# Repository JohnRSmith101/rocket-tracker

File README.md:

# Rocket Tracker

A system that tracks and video-records rockets as they climb into space. A
motorized telescope-and-camera gimbal is steered by an operator until a small
tracking camera sees the rocket. A neural-network detector on a Raspberry Pi 5
then takes over and keeps the rocket centered while the telescope camera
records.

The complete story of why it is built this way, and how to build one yourself,
is in the **Build Book** (see below). This repository has the software,
trained models, hardware design files and training dataset.

## How it works

1. An operator slews the system by joystick, looking through a finder scope, to
   bring the rising rocket into the tracking camera's field of view.
2. A Raspberry Pi 5 runs an object detector (YOLO11n, exported to NCNN) on the
   tracking camera's video. Each time it detects the rocket, it plays an alert
   sound. This tells the operator, who cannot look at a screen, to release the
   joystick trigger.
3. The Pi sends the rocket's position and velocity to an Arduino Due over USB
   serial. The Arduino runs closed-loop PID control of the azimuth and
   elevation stepper motors to keep the rocket centered. The telescope's own
   camera (a Canon EOS 70D on a Celestron C5) records the launch.
4. When detections stop, the alert stops, and the operator can take over.

## What is where

| Folder | Contents |
|---|---|
| `software/gimbal-controller/` | Arduino Due sketches: gimbal controller, and a version that logs PID data |
| `software/tracker-yolo/` | Raspberry Pi 5 tracking program using the YOLO11n model (current) |
| `software/tracker-tflite-legacy/` | Earlier tracking program using a TensorFlow Lite model (kept for reference) |
| `models/yolo/` | The trained YOLO model that Rocket Tracker uses, and training results |
| `models/tflite-ssd-oct2024/` | The earlier TensorFlow Lite model, used by the legacy tracker |
| `models/mediapipe-dec2024/` | A MediaPipe Model Maker model from December 2024, with training records |
| `datasets/` | The 633-image training dataset (documentation here, files in a Release) |
| `hardware/kicad/` | KiCad files and Gerbers for the Gimbal Controller Box and Lid circuit boards |
| `hardware/3d-printing/` | STL files for the 3D-printed parts (print in PETG) |
| `docs/` | Original drawings (the Build Book itself is on the Releases page) |
| `LICENSES/`, `LICENSE`, `NOTICE` | Licensing and credits |

## Downloads (large files)

GitHub limits file sizes in the repository, so these are on the
[Releases page](../../releases):

- **Build Book** (PDF and Word): the full design document
- `rocket-tracker-dataset-633-images.zip`: all images, with YOLO, Pascal VOC and COCO-JSON annotations
- `data.zip`: the same dataset packaged for the YOLO training notebook in Google Colab
- `yolo-training-runs-full.zip`: all three YOLO training runs with weights and plots

## Quick start (YOLO tracker)

1. Build the hardware following the Build Book.
2. On the Raspberry Pi 5, follow the Build Book section "Deploying YOLO models to Raspberry Pi 5", or see `software/tracker-yolo/README.md`.
3. Upload `software/gimbal-controller/Rocket_Tracker_2026_R14` to the Arduino Due.

## Status and limits

- The YOLO model was trained on only 633 images, many of them near-duplicates, and some classes
  have very few examples. Expect it to work best in conditions similar to the training footage.
  See `datasets/README.md`.
- The author built and tested this one system. Other hardware may need changes.
- The TensorFlow Lite and MediaPipe material is kept as a record; the YOLO tracker supersedes it.

## Safety

Motorized mounts can pinch fingers, and optics can cause permanent eye damage if pointed at the
sun. Build and operate at your own risk. See `LICENSE`.

## License

Open source, with different licenses for different parts: Apache-2.0 (Arduino and TFLite
software), AGPL-3.0 (YOLO tracker and models), CC BY-SA 4.0 (Build Book, hardware, datasets).
Details in `LICENSE`. Credits to the projects this builds on are in `NOTICE`.

Copyright 2026 John R. Smith.

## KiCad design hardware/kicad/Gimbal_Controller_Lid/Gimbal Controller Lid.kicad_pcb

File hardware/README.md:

# Hardware

License: CC BY-SA 4.0.

- `kicad/`: KiCad projects for the Gimbal Controller circuit boards (**Box** and **Lid**). Each folder has the KiCad project, schematic and PCB files, a picture, and a zip of the Gerber and drill files for ordering boards.
- `3d-printing/`: one folder per part, each with an STL file and a preview picture. Print in PETG. The parts were designed in the Morphi app (iPad) and sliced in Ultimaker Cura for an Ender 3 printer. See the Build Book, Appendix A, for the parts list and photos.

The Build Book has the wiring, the complete parts list, and assembly instructions.

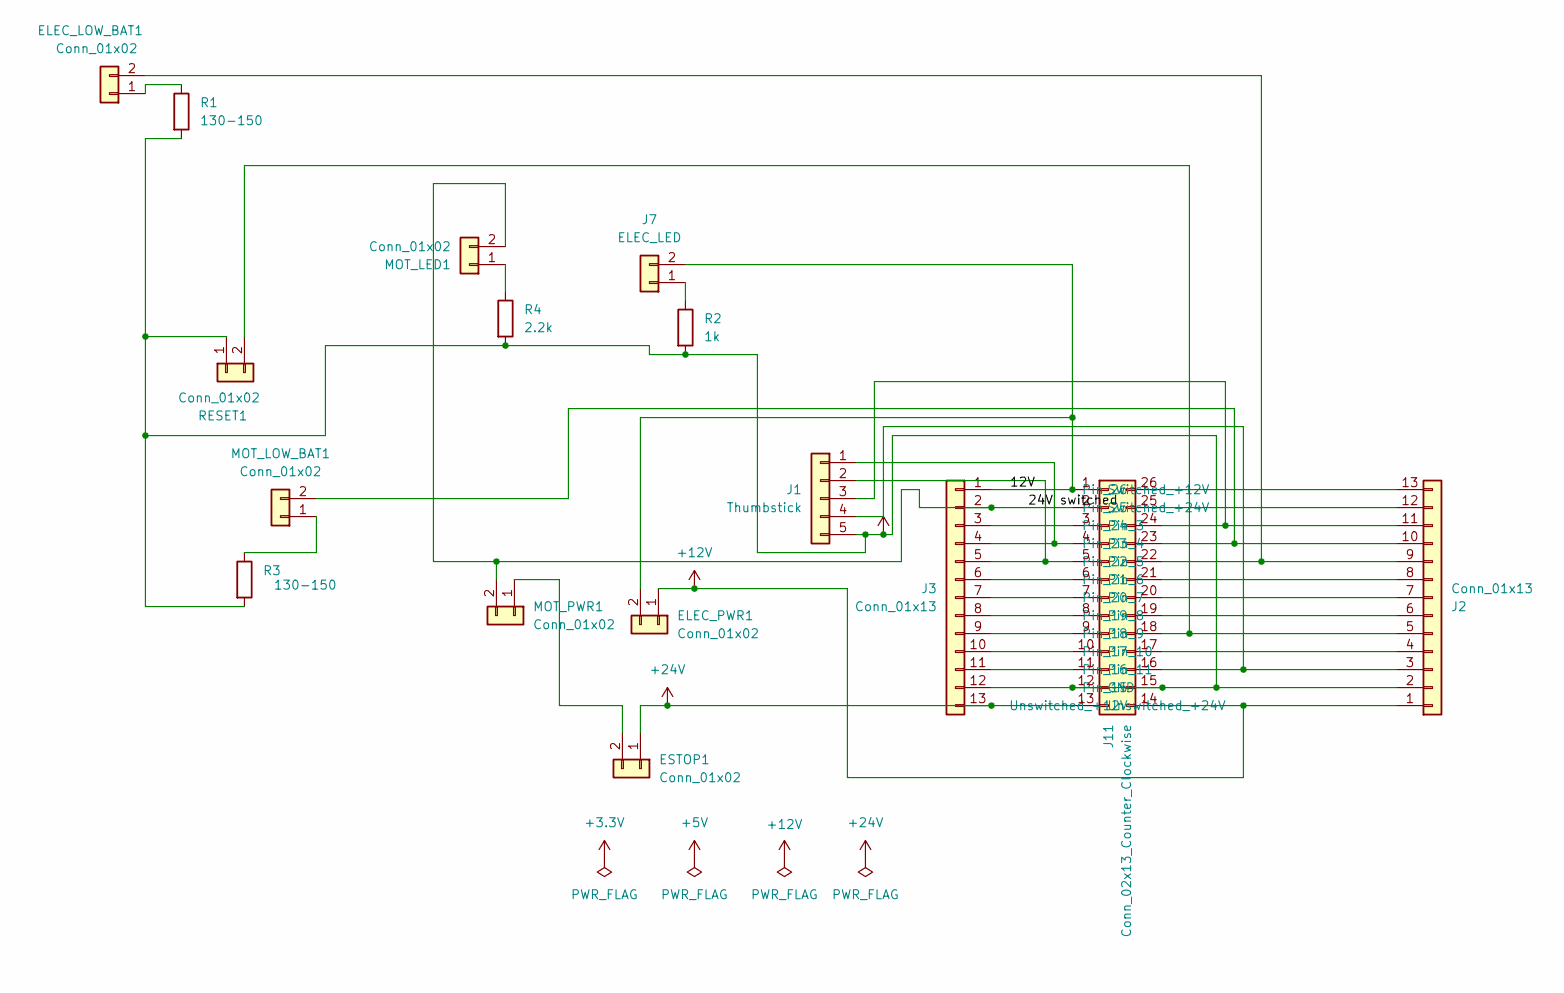
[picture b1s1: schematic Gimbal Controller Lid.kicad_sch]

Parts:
ELEC_LOW_BAT1: Conn_01x02; PinSocket_1x02_P2.54mm_Vertical
ELEC_PWR1: Conn_01x02; PinSocket_1x02_P2.54mm_Vertical
ESTOP1: Conn_01x02; PinSocket_1x02_P2.54mm_Vertical
J1: Thumbstick; PinHeader_1x05_P2.54mm_Vertical
J2, J3: Conn_01x13; PinSocket_1x13_P2.54mm_Vertical
J7: ELEC_LED; PinSocket_1x02_P2.54mm_Vertical
J11: Conn_02x13_Counter_Clockwise; IDC-Header_2x13_P2.54mm_Vertical
MOT_LED1: Conn_01x02; PinSocket_1x02_P2.54mm_Vertical
MOT_LOW_BAT1: Conn_01x02; PinSocket_1x02_P2.54mm_Vertical
MOT_PWR1: Conn_01x02; PinSocket_1x02_P2.54mm_Vertical
R1, R3: 130-150; R_Axial_DIN0204_L3.6mm_D1.6mm_P7.62mm_Horizontal
R2: 1k; R_Axial_DIN0204_L3.6mm_D1.6mm_P7.62mm_Horizontal
R4: 2.2k; R_Axial_DIN0204_L3.6mm_D1.6mm_P7.62mm_Horizontal
RESET1: Conn_01x02; PinSocket_1x02_P2.54mm_Vertical

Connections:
+5V: J1.5, J2.2, J3.12, J11.12 (GND), J11.15, R1.2, R2.2, R3.2, R4.2, RESET1.1
+12V: ELEC_PWR1.1, J2.1, J11.14 (Unswitched_+12V)
+24V: ESTOP1.1, J3.13, J11.13 (Unswitched_+24V)
/12V: ELEC_PWR1.2, J3.1, J7.2, J11.1 (Switched_+12V)
/24V switched: J3.2, J11.2 (Switched_+24V), MOT_LED1.2, MOT_PWR1.2
unnamed: ELEC_LOW_BAT1.1, R1.1
unnamed: ELEC_LOW_BAT1.2, J2.9, J11.22
unnamed: ESTOP1.2, MOT_PWR1.1
unnamed: J1.1, J3.4, J11.4
unnamed: J1.2, J3.5, J11.5
unnamed: J1.3, J2.11, J11.24
unnamed: J1.4, J2.3, J11.16
unnamed: J7.1, R2.1
unnamed: J3.3, J11.3
unnamed: J3.6, J11.6
unnamed: J3.7, J11.7
unnamed: J3.8, J11.8
unnamed: J3.9, J11.9
unnamed: J3.10, J11.10
unnamed: J3.11, J11.11
unnamed: J2.4, J11.17
unnamed: J2.5, J11.18, RESET1.2
unnamed: J2.6, J11.19
unnamed: J2.7, J11.20
unnamed: J2.8, J11.21
unnamed: J2.10, J11.23, MOT_LOW_BAT1.2
unnamed: J2.12, J11.25
unnamed: J2.13, J11.26
unnamed: MOT_LED1.1, R4.1
unnamed: MOT_LOW_BAT1.1, R3.1

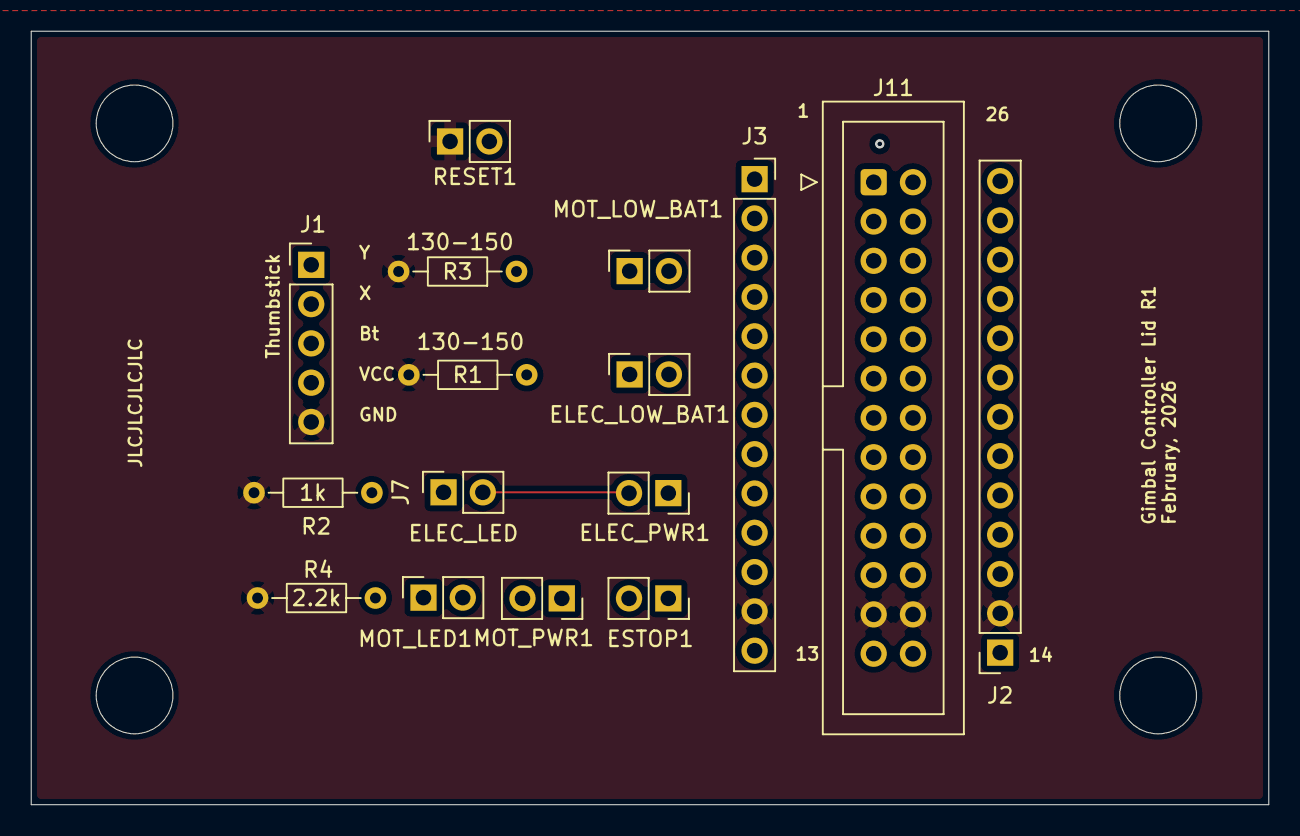
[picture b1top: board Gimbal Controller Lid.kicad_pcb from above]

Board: 4 copper layers, 80.0 x 50.0 mm, 16 parts (0 on the bottom side), 30 nets.

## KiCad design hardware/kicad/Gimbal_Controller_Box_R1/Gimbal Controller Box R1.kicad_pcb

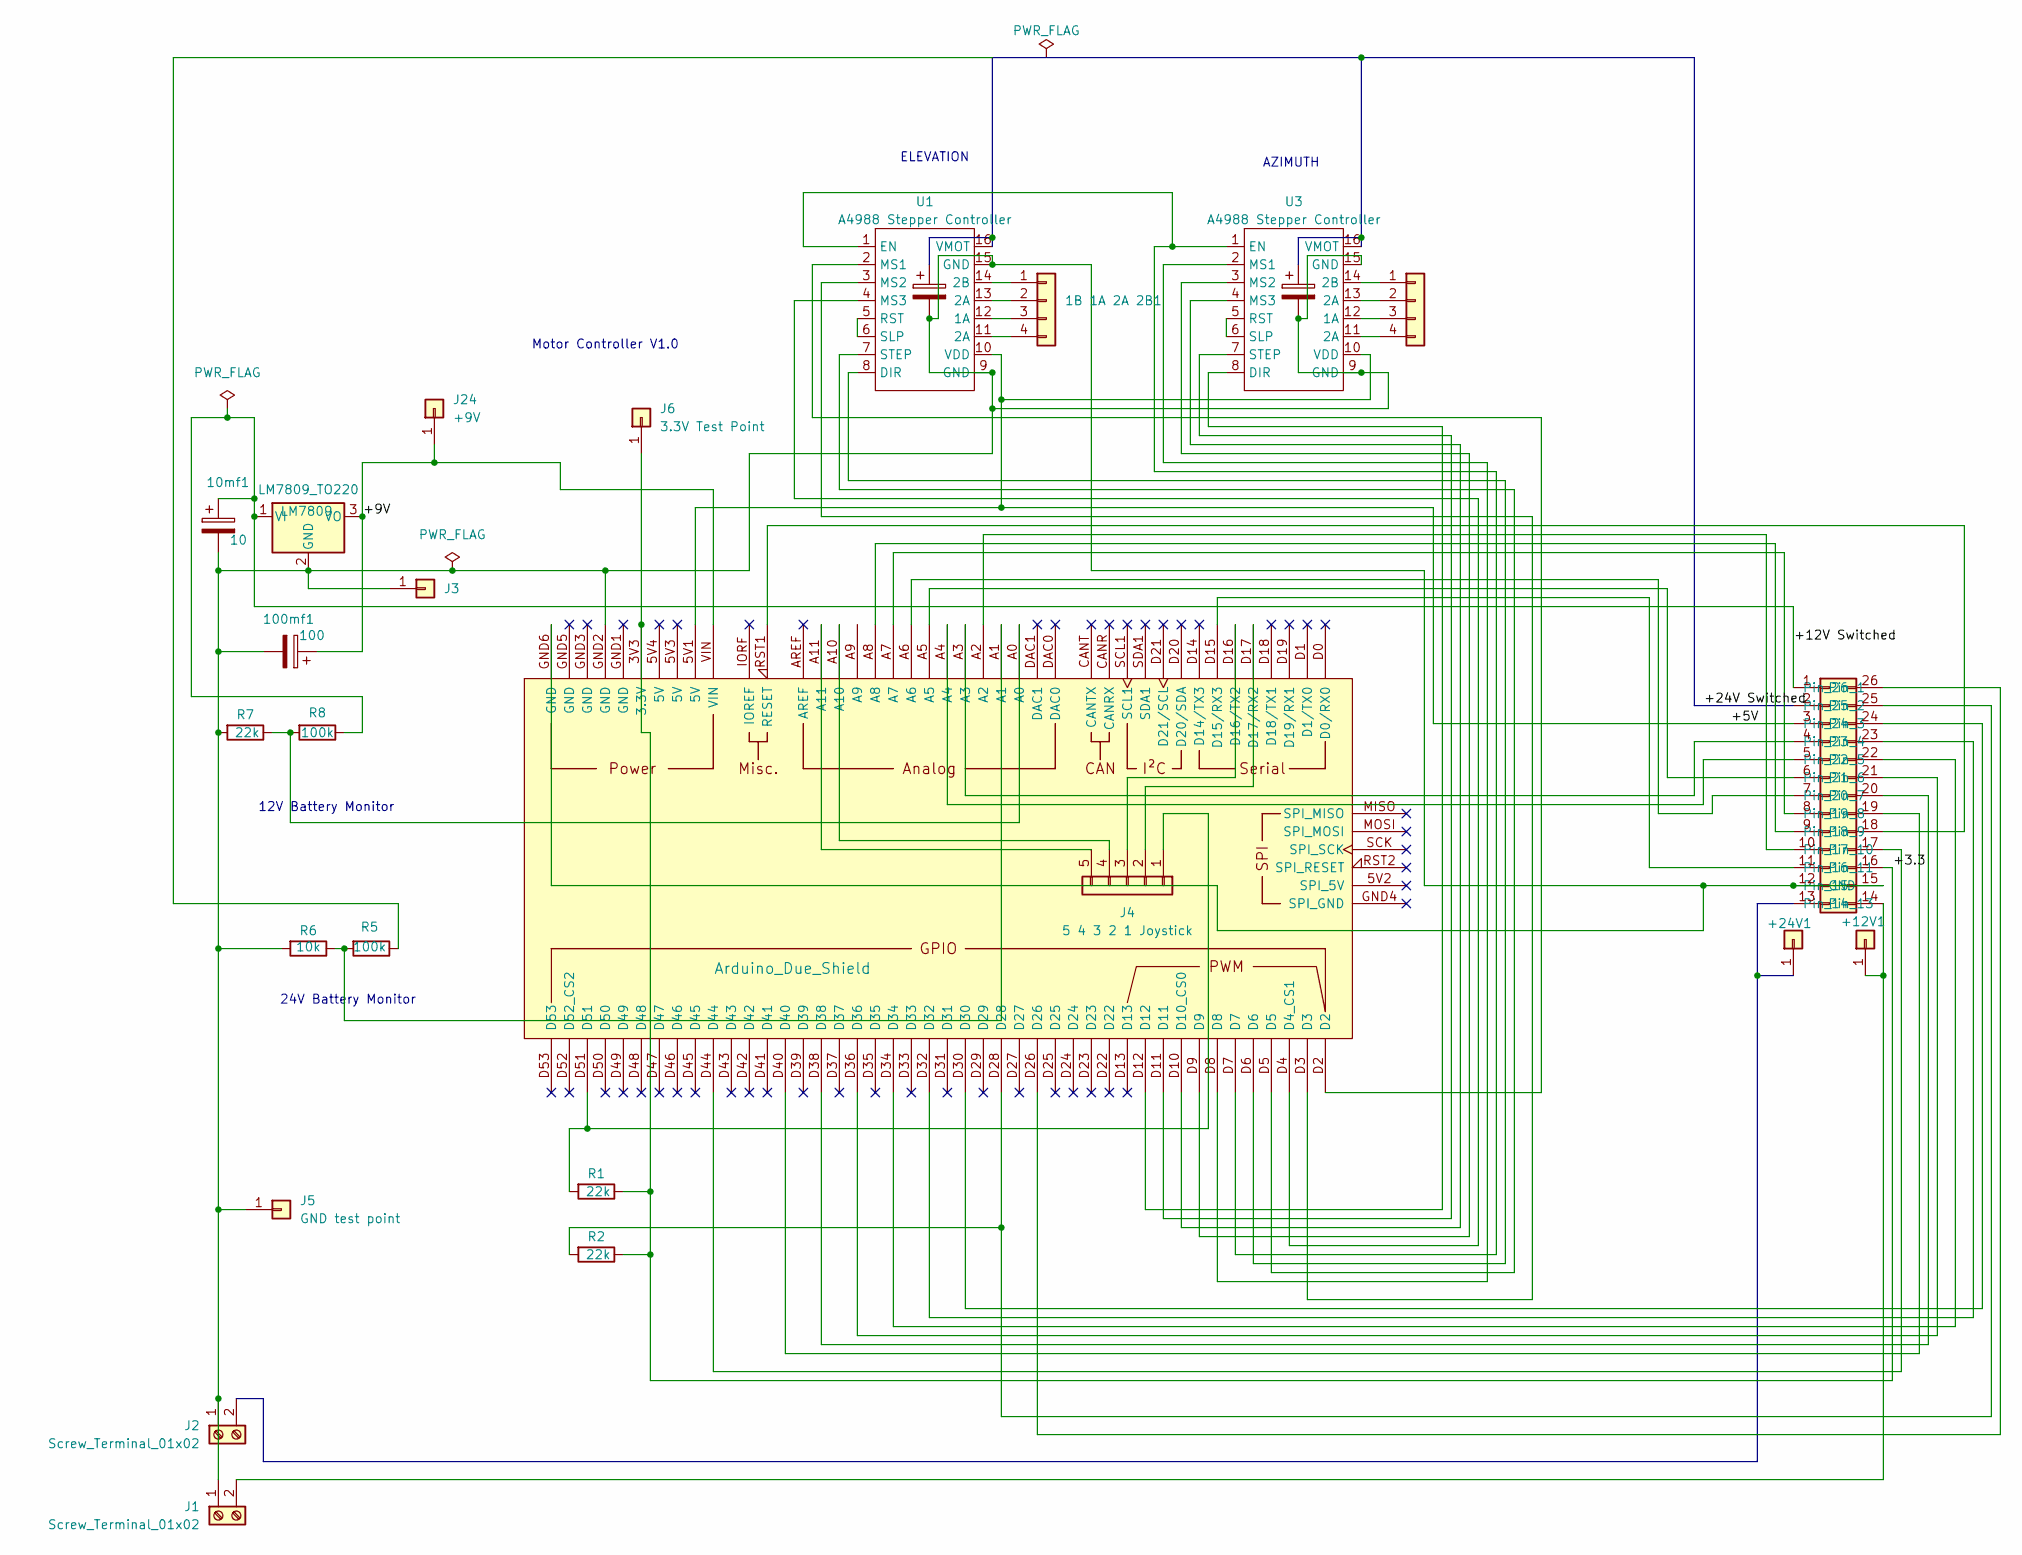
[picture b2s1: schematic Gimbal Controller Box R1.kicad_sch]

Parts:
1B 1A 2A 2B1, 1B 1A 2A 2B2: Conn_01x04; PinSocket_1x04_P2.54mm_Vertical
10mf1: 10; CP_Radial_D5.0mm_P2.50mm
100mf1: 100; CP_Radial_D5.0mm_P2.50mm
+12V1, +24V1: Conn_01x01; PinHeader_1x01_P2.54mm_Vertical
A1: Arduino_Due_Shield
C1, C6: C_Polarized; CP_Radial_D5.0mm_P2.50mm
J1, J2: Screw_Terminal_01x02; Altech_AK100_1x02_P5.00mm
J3: GND; PinHeader_1x01_P2.54mm_Vertical
J4: 5 4 3 2 1 Joystick; PinHeader_1x05_P2.54mm_Vertical
J5: GND test point; PinHeader_1x01_P2.54mm_Vertical
J6: 3.3V Test Point; PinHeader_1x01_P2.54mm_Vertical
J11: Conn_02x13_Counter_Clockwise; IDC-Header_2x13_P2.54mm_Vertical
J24: +9V; PinHeader_1x01_P2.54mm_Vertical
LM7809: LM7809_TO220; TO-220-3_Vertical
R1, R2, R7: 22k; R_Axial_DIN0207_L6.3mm_D2.5mm_P7.62mm_Horizontal
R5, R8: 100k; R_Axial_DIN0207_L6.3mm_D2.5mm_P7.62mm_Horizontal
R6: 10k; R_Axial_DIN0207_L6.3mm_D2.5mm_P7.62mm_Horizontal
U1, U3: A4988 Stepper Controller; A4988 Controller (Alternate)

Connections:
/+3.3: A1.3V3 (3.3V), J6.1, J11.16, R1.1, R2.1
/+5V: A1.5V1 (5V), J11.3, U1.10 (VDD), U3.10 (VDD)
/+9V: 100mf1.1, A1.VIN, J24.1, LM7809.3 (VO)
/+12V Switched: 10mf1.1, J11.1, LM7809.1 (VI), R8.1
/+24V Switched: C1.1, C6.1, J11.2, U1.16 (VMOT), U3.16 (VMOT)
unnamed: 1B 1A 2A 2B1.1, U1.14 (2B)
unnamed: 1B 1A 2A 2B1.2, U1.13 (2A)
unnamed: 1B 1A 2A 2B1.3, U1.12 (1A)
unnamed: 1B 1A 2A 2B1.4, U1.11 (2A)
unnamed: 1B 1A 2A 2B2.1, U3.14 (2B)
unnamed: 1B 1A 2A 2B2.2, U3.13 (2A)
unnamed: 1B 1A 2A 2B2.3, U3.12 (1A)
unnamed: 1B 1A 2A 2B2.4, U3.11 (2A)
unnamed: +12V1.1, J1.2, J11.14
unnamed: +24V1.1, J2.2, J11.13
unnamed: A1.D4 (D4_CS1), U1.4 (MS3)
unnamed: A1.D10 (D10_CS0), U3.4 (MS3)
unnamed: A1.D15 (D15/RX3), J11.11
unnamed: A1.D16 (D16/TX2), J4.3
unnamed: A1.D17 (D17/RX2), J4.2
unnamed: A1.A0, R7.1, R8.2
unnamed: A1.A1, R5.2, R6.1
unnamed: A1.RST1 (RESET), J11.18
unnamed: 10mf1.2, 100mf1.2, A1.GND2 (GND), A1.GND6 (GND), C1.2, C6.2, J1.1, J2.1, J3.1, J5.1, J11.12 (GND), J11.15, LM7809.2 (GND), R6.2, R7.2, U1.9 (GND), U1.15 (GND), U3.9 (GND), U3.15 (GND)
unnamed: A1.D51, J4.1, R1.2
unnamed: A1.A10, J4.4
unnamed: A1.A11, J4.5
unnamed: A1.A3, J11.4
unnamed: A1.A4, J11.5
unnamed: A1.A5, J11.6
unnamed: A1.A6, J11.7
unnamed: A1.A7, J11.8
unnamed: A1.A8, J11.9
unnamed: A1.A2, J11.10
unnamed: A1.D44, J11.17
unnamed: A1.D40, J11.19
unnamed: A1.D38, J11.20
unnamed: A1.D36, J11.21
unnamed: A1.D34, J11.22
unnamed: A1.D32, J11.23
unnamed: A1.D30, J11.24
unnamed: A1.D28, J11.25, R2.2
unnamed: A1.D26, J11.26
unnamed: A1.D6, U1.8 (DIR)
unnamed: A1.D7, U1.1 (EN), U3.1 (EN)
unnamed: A1.D2, U1.2 (MS1)
unnamed: A1.D3, U1.3 (MS2)
unnamed: U1.5 (RST), U1.6 (SLP)
unnamed: A1.D5, U1.7 (STEP)
unnamed: A1.D12, U3.8 (DIR)
unnamed: A1.D8, U3.2 (MS1)
unnamed: A1.D9, U3.3 (MS2)
unnamed: U3.5 (RST), U3.6 (SLP)
unnamed: A1.D11, U3.7 (STEP)

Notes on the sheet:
AZIMUTH
24V Battery Monitor
12V Battery Monitor
ELEVATION
Motor Controller V1.0

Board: 4 copper layers, 26 parts (0 on the bottom side), 54 nets, no tracks yet.
